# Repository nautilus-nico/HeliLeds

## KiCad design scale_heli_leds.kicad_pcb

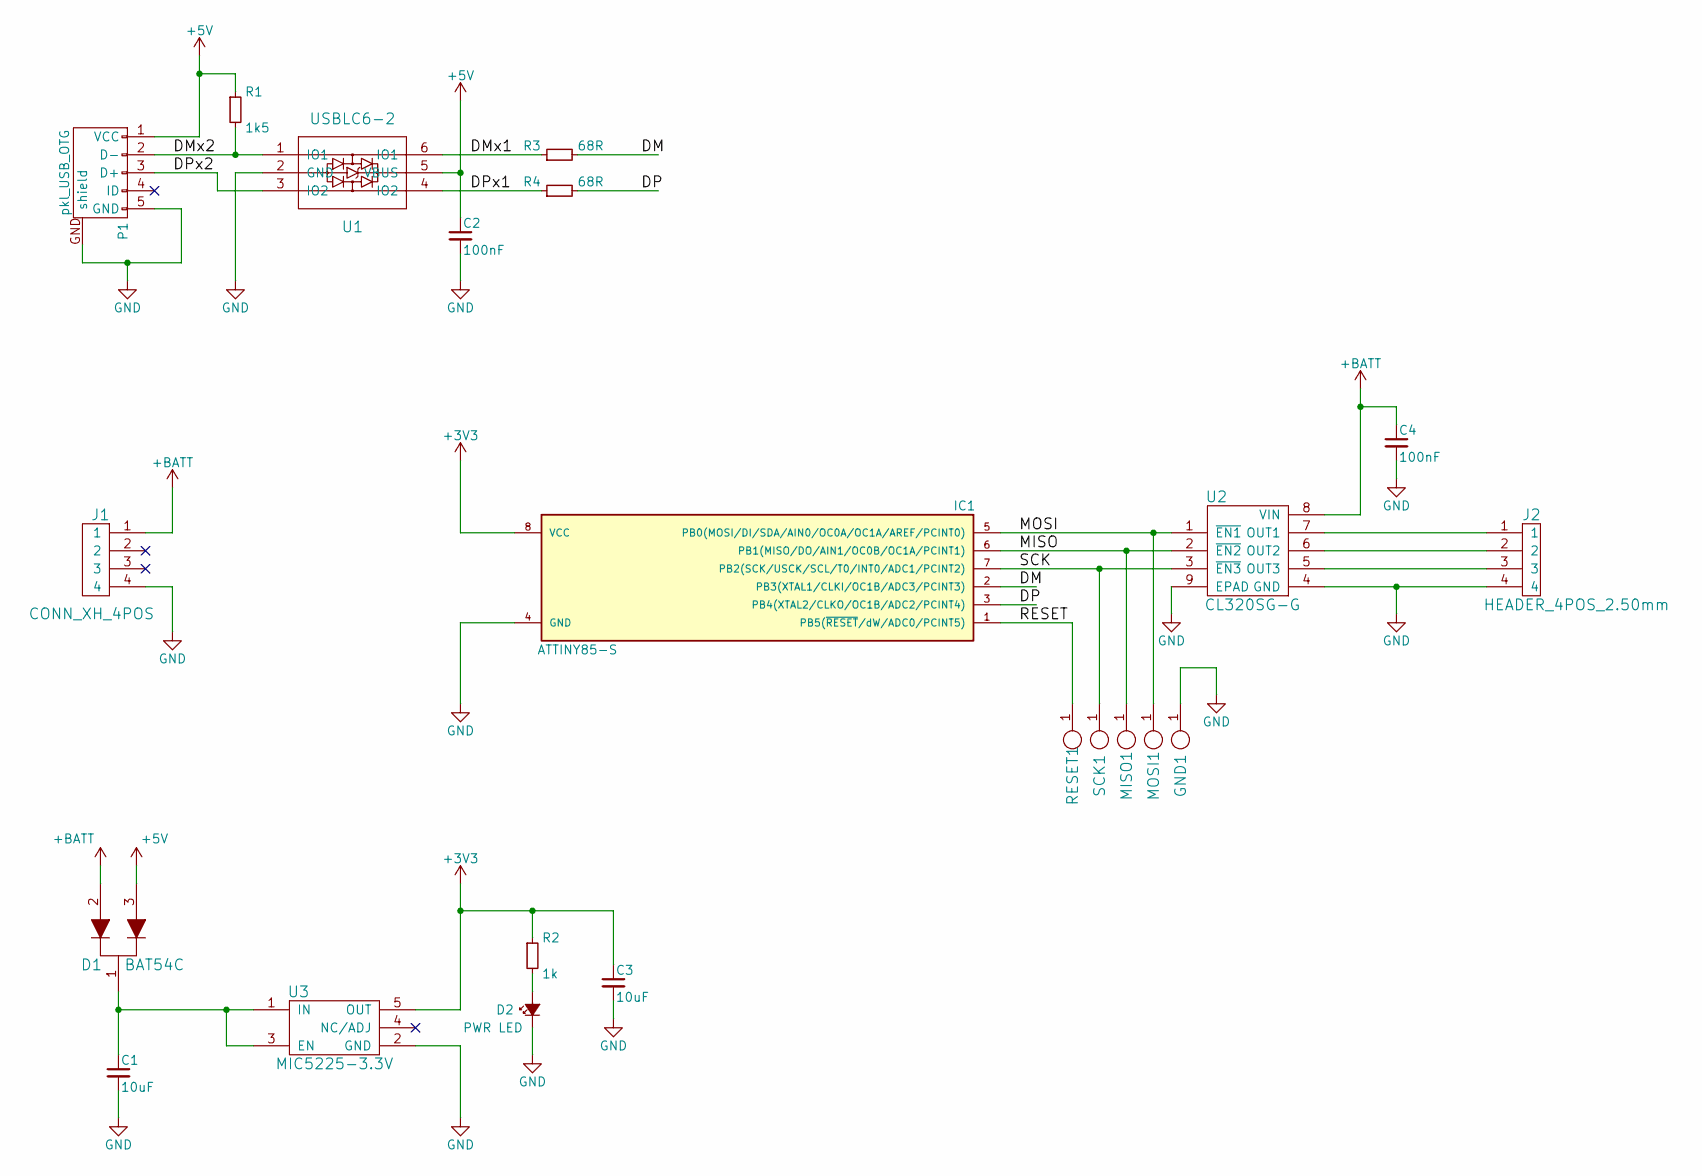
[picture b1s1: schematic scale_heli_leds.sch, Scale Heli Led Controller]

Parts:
C1, C3: 10uF; C_0603_HandSoldering
C2, C4: 100nF; C_0603_HandSoldering
D1: BAT54C; SOT-23-3; MPN BAT54C; Digi-Key_PN BAT54CFSCT-ND
D2: PWR LED; LED_0603_HandSoldering
GND1: POGO_PAD_SMD; PAD_SMD_R_1x1
IC1: ATTINY85-S; SOIC-8_5.3x5.3mm_Pitch1.27mm
J1: CONN_XH_4POS; Pin_Header_Angled_1x04
J2: HEADER_4POS_2.50mm; Pin_Header_Straight_1x04
MISO1: POGO_PAD_SMD; PAD_SMD_R_1x1
MOSI1: POGO_PAD_SMD; PAD_SMD_R_1x1
P1: pkl_USB_OTG; Connector_USB_Micro_B_SMD
R1: 1k5; R_0603_HandSoldering
R2: 1k; R_0603_HandSoldering
R3, R4: 68R; R_0603_HandSoldering
RESET1: RESET; PAD_SMD_R_1x1
SCK1: POGO_PAD_SMD; PAD_SMD_R_1x1
U1: USBLC6-2; SOT-666
U2: CL320SG-G; SOIC-8-1EP_3.9x4.9mm_Pitch1.27mm
U3: MIC5225-3.3V; SOT-23-5

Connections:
+3V3: C3.1, IC1.8 (VCC), R2.1, U3.5 (OUT)
+5V: C2.1, D1.3, P1.1 (VCC), R1.1, U1.5 (VBUS)
+BATT: C4.1, D1.2, J1.1, U2.8 (VIN)
/DM: IC1.2 (PB3(XTAL1/CLKI/OC1B/ADC3/PCINT3)), R3.2
/DMx1: R3.1, U1.6 (IO1)
/DMx2: P1.2 (D-), R1.2, U1.1 (IO1)
/DP: IC1.3 (PB4(XTAL2/CLKO/OC1B/ADC2/PCINT4)), R4.2
/DPx1: R4.1, U1.4 (IO2)
/DPx2: P1.3 (D+), U1.3 (IO2)
/MISO: IC1.6 (PB1(MISO/DO/AIN1/OC0B/OC1A/PCINT1)), MISO1.1, U2.2 (~EN2)
/MOSI: IC1.5 (PB0(MOSI/DI/SDA/AIN0/OC0A/OC1A/AREF/PCI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), MOSI1.1, U2.1 (~EN1)
/RESET: IC1.1 (PB5(~RESET~/dW/ADC0/PCINT5)), RESET1.1
/SCK: IC1.7 (PB2(SCK/USCK/SCL/T0/INT0/ADC1/PCINT2)), SCK1.1, U2.3 (~EN3)
GND: C1.2, C2.2, C3.2, C4.2, D2.1 (K), GND1.1, IC1.4 (GND), J1.4, J2.4, P1.5 (GND), P1.GND (shield), U1.2 (GND), U2.4 (GND), U2.9 (EPAD), U3.2 (GND)
unnamed: C1.1, D1.1, U3.1 (IN), U3.3 (EN)
unnamed: D2.2 (A), R2.2
unnamed: J2.1, U2.7 (OUT1)
unnamed: J2.2, U2.6 (OUT2)
unnamed: J2.3, U2.5 (OUT3)

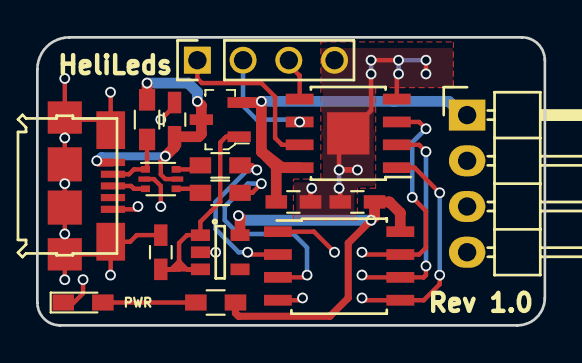
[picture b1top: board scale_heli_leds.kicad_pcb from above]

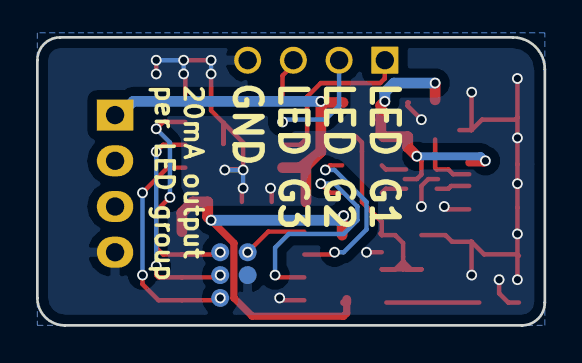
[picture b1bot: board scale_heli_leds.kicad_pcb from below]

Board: 2 copper layers, 28.2 x 16.0 mm, 22 parts (5 on the bottom side), 19 nets.

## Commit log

2018-11-13 Updated to Rev1.1: Fixed battery connector orientation, fixed incorrect BAT54C schematic symbol pin numbers, removed programming pads.
